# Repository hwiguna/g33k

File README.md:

g33k
====

Personal code, mostly for my blog g33k.blogspot.com

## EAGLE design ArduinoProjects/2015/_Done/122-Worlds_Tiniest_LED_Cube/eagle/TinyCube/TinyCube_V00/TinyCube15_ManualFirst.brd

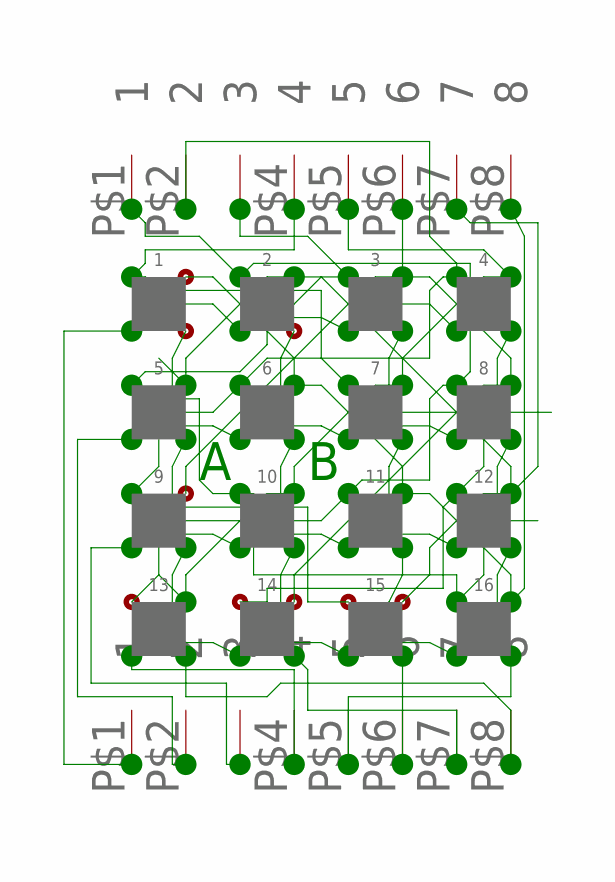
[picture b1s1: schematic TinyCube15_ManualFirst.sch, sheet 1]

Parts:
1, 2, 3, 4, 5, 6, 7, 8, 9, 10, 11, 12, 13, 14, 15, 16: PILLAR; 10MIL
U$51, U$52: TINY_HEADER_DEV; TINY_HEADER_PKG

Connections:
unnamed: 1.R (B), 7.R (B), 12.R (B), 14.R (B), U$52.P$4 (4)
unnamed: 4.B (R), 8.B (R), 12.B (R), 16.B (R), U$51.P$5 (5)
unnamed: 3.B (R), 7.B (R), 11.B (R), 15.B (R), U$51.P$6 (6)
unnamed: 2.B (R), 6.B (R), 10.B (R), 14.B (R), U$51.P$7 (7)
unnamed: 1.+ (G), 6.+ (G), 11.+ (G), 16.+ (G), U$52.P$8 (8)
unnamed: 2.R (B), 8.R (B), 11.R (B), 13.R (B), U$52.P$1 (1)
unnamed: 1.G (A), 2.G (A), 3.G (A), 4.G (A), U$51.P$1 (1)
unnamed: 5.G (A), 6.G (A), 7.G (A), 8.G (A), U$51.P$2 (2)
unnamed: 9.G (A), 10.G (A), 11.G (A), 12.G (A), U$51.P$3 (3)
unnamed: 13.G (A), 14.G (A), 15.G (A), 16.G (A), U$51.P$4 (4)
unnamed: 4.R (B), 6.R (B), 9.R (B), 15.R (B), U$52.P$2 (2)
unnamed: 2.+ (G), 5.+ (G), 12.+ (G), 15.+ (G), U$52.P$7 (7)
unnamed: 3.+ (G), 8.+ (G), 9.+ (G), 14.+ (G), U$52.P$6 (6)
unnamed: 1.B (R), 5.B (R), 9.B (R), 13.B (R), U$51.P$8 (8)
unnamed: 4.+ (G), 7.+ (G), 10.+ (G), 13.+ (G), U$52.P$5 (5)
unnamed: 3.R (B), 5.R (B), 10.R (B), 16.R (B), U$52.P$3 (3)

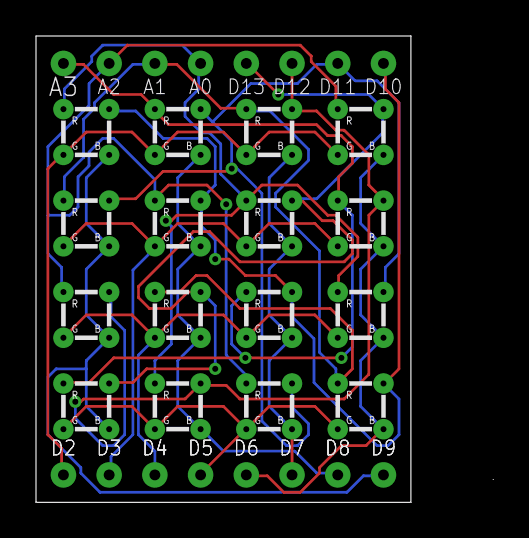
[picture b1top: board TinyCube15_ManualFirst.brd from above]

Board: 2 copper layers, 25.4 x 25.9 mm, 18 parts (0 on the bottom side), 16 nets.

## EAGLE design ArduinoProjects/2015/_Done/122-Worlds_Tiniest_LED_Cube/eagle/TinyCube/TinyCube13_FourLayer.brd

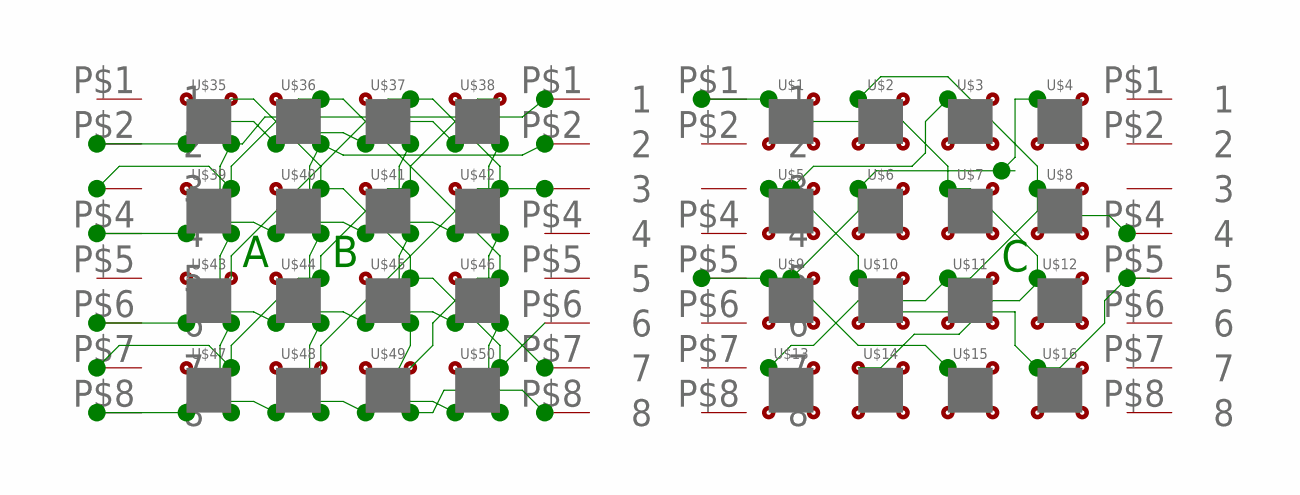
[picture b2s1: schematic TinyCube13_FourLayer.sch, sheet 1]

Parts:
JP1, JP2: TINY_HEADER_DEV; TINY_HEADER_PKG
U$1, U$2, U$3, U$4, U$5, U$6, U$7, U$8, U$9, U$10, U$11, U$12, U$13, U$14, U$15, U$16, U$35, U$36, U$37, U$38, U$39, U$40, U$41, U$42, U$43, U$44, U$45, U$46, U$47, U$48, U$49, U$50: PILLAR; 10MIL
U$51, U$52: TINY_HEADER_DEV; TINY_HEADER_PKG

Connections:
unnamed: JP2.P$4 (4), U$2.R (B), U$8.R (B), U$11.R (B), U$13.R (B)
unnamed: JP1.P$1 (1), U$1.R (B), U$7.R (B), U$12.R (B), U$14.R (B)
unnamed: JP2.P$5 (5), U$3.R (B), U$5.R (B), U$10.R (B), U$16.R (B)
unnamed: JP1.P$5 (5), U$4.R (B), U$6.R (B), U$9.R (B), U$15.R (B)
unnamed: U$35.+ (G), U$40.+ (G), U$45.+ (G), U$50.+ (G), U$52.P$6 (6)
unnamed: U$35.G (A), U$36.G (A), U$37.G (A), U$38.G (A), U$51.P$2 (2)
unnamed: U$39.G (A), U$40.G (A), U$41.G (A), U$42.G (A), U$51.P$4 (4)
unnamed: U$43.G (A), U$44.G (A), U$45.G (A), U$46.G (A), U$51.P$6 (6)
unnamed: U$47.G (A), U$48.G (A), U$49.G (A), U$50.G (A), U$51.P$8 (8)
unnamed: U$35.B (R), U$39.B (R), U$43.B (R), U$47.B (R), U$52.P$1 (1)
unnamed: U$37.B (R), U$41.B (R), U$45.B (R), U$49.B (R), U$52.P$8 (8)
unnamed: U$38.B (R), U$42.B (R), U$46.B (R), U$50.B (R), U$52.P$7 (7)
unnamed: U$36.B (R), U$40.B (R), U$44.B (R), U$48.B (R), U$52.P$2 (2)
unnamed: U$36.+ (G), U$39.+ (G), U$46.+ (G), U$49.+ (G), U$51.P$3 (3)
unnamed: U$37.+ (G), U$42.+ (G), U$43.+ (G), U$48.+ (G), U$52.P$3 (3)
unnamed: U$38.+ (G), U$41.+ (G), U$44.+ (G), U$47.+ (G), U$51.P$7 (7)

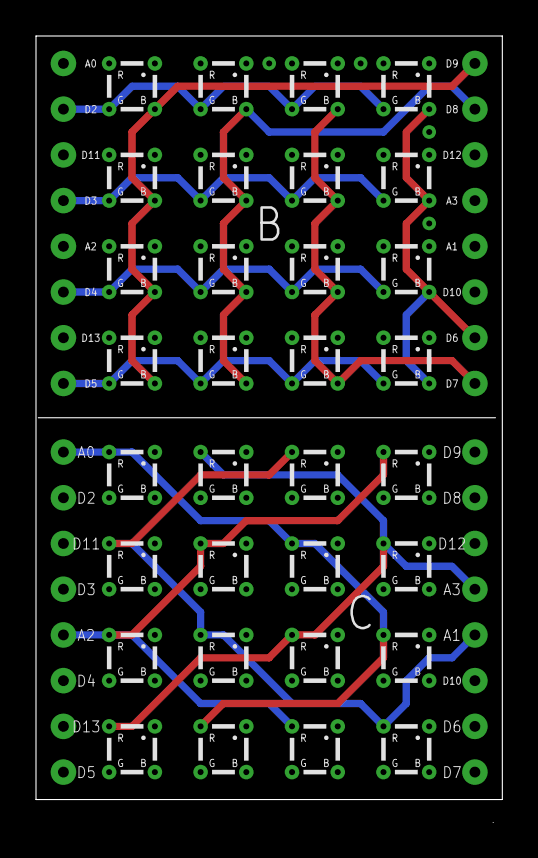
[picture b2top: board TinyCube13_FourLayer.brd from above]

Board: 4 copper layers, 25.9 x 43.7 mm, 36 parts (0 on the bottom side), 16 nets.

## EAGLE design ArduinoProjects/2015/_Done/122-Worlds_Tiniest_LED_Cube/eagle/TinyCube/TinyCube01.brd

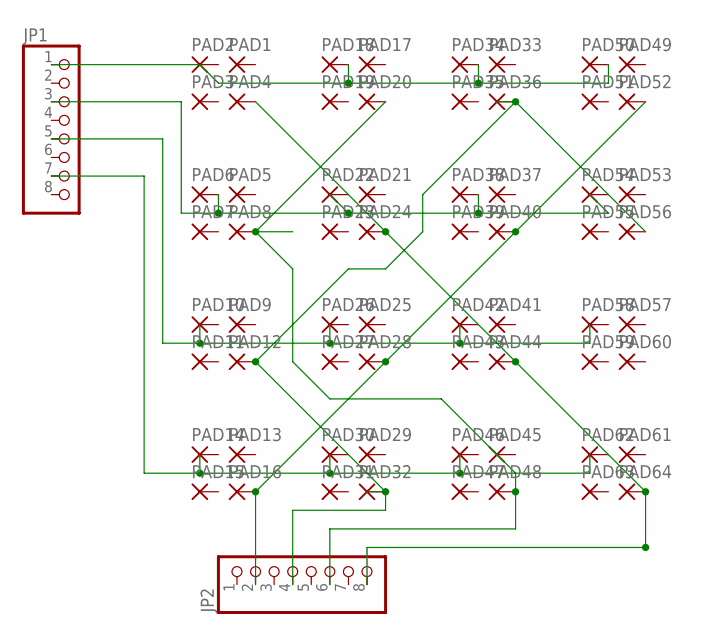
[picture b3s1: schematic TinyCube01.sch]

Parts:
JP1, JP2: PINHD-1X8BIG; 1X08-BIG
PAD1, PAD2, PAD3, PAD4, PAD5, PAD6, PAD7, PAD8, PAD9, PAD10, PAD11, PAD12, PAD13, PAD14, PAD15, PAD16, PAD17, PAD18, PAD19, PAD20, PAD21, PAD22, PAD23, PAD24, PAD25, PAD26, PAD27, PAD28, PAD29, PAD30, PAD31, PAD32, PAD33, PAD34, PAD35, PAD36, PAD37, PAD38, PAD39, PAD40, PAD41, PAD42, PAD43, PAD44, PAD45, PAD46, PAD47, PAD48, PAD49, PAD50, PAD51, PAD52, PAD53, PAD54, PAD55, PAD56, PAD57, PAD58, PAD59, PAD60, PAD61, PAD62, PAD63, PAD64: SMALLPADTHROUGH-HOLE-SMALL; SMALLPAD

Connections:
unnamed: JP2.2, PAD16.1, PAD28.1, PAD40.1, PAD52.1
unnamed: JP2.8, PAD4.1, PAD24.1, PAD44.1, PAD64.1
unnamed: JP2.6, PAD8.1, PAD20.1, PAD48.1
unnamed: JP1.1, PAD18.1, PAD34.1, PAD50.1
unnamed: JP1.3, PAD6.1, PAD38.1
W10: JP2.4, PAD12.1, PAD32.1, PAD36.1, PAD56.1

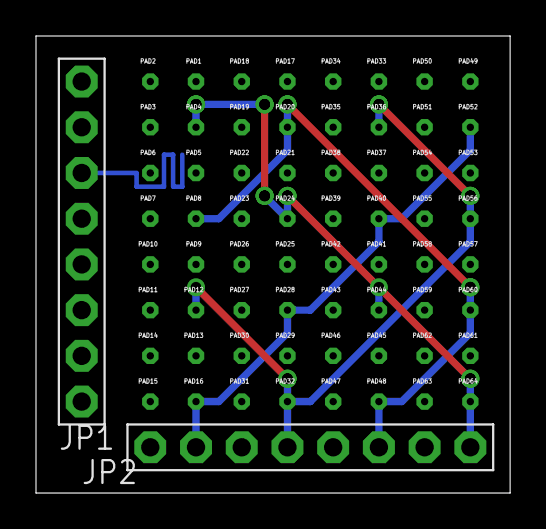
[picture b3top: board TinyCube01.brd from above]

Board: 2 copper layers, 26.3 x 25.4 mm, 66 parts (0 on the bottom side), 6 nets.

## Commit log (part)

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2013-03-22 First version shared on blog
    Uses TIMER, does Fireworks and Bounces.
2013-04-14 First checkin
2014-03-06 Learning how to do interrrupts, figure out the LED matrix pinouts
2014-03-06 Got the shift registers today. Learn how to shift two bytes. Liked MSBFirst shiftOut()
2014-03-07 Move all Tetris related project files into one folder
2014-03-08 Prefix folders with chronological number
2014-03-08 Got interrupt refresh working! Woohoo!
2014-03-08 More comments
2014-03-09 Create and test Tetris shapes
2014-03-10 More analog pins
2014-03-10 Seeing if analogRead works alongside with interrupts
2014-03-10 Let's see if we can control a piece with the accelerometer
2014-03-10 More accelerometer experiments. This one works quite well.
2014-03-10 Figure out when a piece hits something on the bitmap
2014-03-12 Learning how to declare and use class in Arduino
2014-03-14 How to pre-initialize a mumti-dimensional array in a class and return it to main
2014-03-15 This version leaves the pile of shapes that reached bottom
2014-03-15 Rewrote collision checks. Also added check to remove full rows.
2014-03-19 Tweaking the playability
2014-03-23 Playing with keyboard matrix
2014-03-26 Not my code. pushed so i have a backup of my settings
2014-04-14 Sync up HariBot
2014-04-14 Worked on keyboard matrix
2014-04-14 Tweaking Hari's Plotclock
2014-04-26 Goofing around with INPUT_PULLUP
2014-04-27 Beware that this version is for Pololu H-Bridge, different than previous versions!!!
2014-05-10 Syncing mac to github
2014-05-10 Code cleanup
2014-05-12 Playing with Python
2014-05-16 Sync
2014-05-16 Put LED Matrix code on GitHub
2014-06-08 More cube code. Documenting my learning step by step
2014-06-09 Uses TimerOne to refresh cube. Verified some test patterns.
2014-06-30 More cube related revisions
2014-07-03 still playing with interrupts
2014-07-11 Scan one layer for Joseph
2014-07-17 Invert output of shift register because I took transistors off there. More patterns.
2014-07-26 This is what's on completed cube video
2014-07-26 Added three touch sensors and two potentiometers
2014-09-01 Added sine wave animation
2014-09-02 Added transition to sine wave
2014-09-04 Line drawing, Wiper animation.
2014-09-08 Added Bresenham3D line drawing routine
2014-09-08 Experimenting with controlling Arduino from C# via serial
2014-09-08 Corner Bursts Animation
2014-09-10 Split into multiple files. More Animations.
2014-09-15 Flea jump
2014-09-21 Easier to use Flea jump no longer require caller to specify rotation
2014-09-21 We got Rain!
2014-09-23 V15 communication with PC app
2014-09-24 Flea Party !
    Unable to get PC to Arduino serial to work reliably, I worked on
    getting multiple fleas on the cube.
2014-09-29 Preparing for TurbineFlats demo. Added Telekinesis.
2014-10-25 vers 16
2014-10-25 Example
2014-10-25 Trinket version
2014-10-25 Playing with NRF24
2014-10-25 Playing with 4x4 keypad
2014-10-25 Initial push
2014-10-25 crap
2014-10-26 Some missed LED stuff
2014-10-26 Adafruit CC3000 stuff
2014-10-26 missed image
2014-10-26 Auto advance, split source into tabs
2014-10-27 Initial Puzzle
2014-10-27 Learning how to implement classes in Arduino
2014-10-27 AdaFruit Libraries
2014-10-27 Initialize board to a sample puzzle
2014-10-29 Using Candidates and Rejected arrays
2014-10-29 using bits to represent Candidates and Rejected
    because we ran out of RAM when we store those as char arrays
2014-11-01 Implement one CellState instead of separate states for solved and candidates
2014-11-01 Nice class hierarchy: Debug, CellState, Cell, Board, Scaner
2014-11-01 starting to scan
2014-11-01 About to combine Cell and CellState
2014-11-02 OMG it finally worked.
    Stupid mistake making debug take in byte instead of int reported
    erroneous zeroes when passing in int to debug. Also has to pass
    pointers instead of objects so values can be changed.
2014-11-02 Cleanup
2014-11-02 successfully solved a few cells. About to refactor to reuse PruneCells
2014-11-02 refactored so we can use one PruneCells()
2014-11-02 One stinking bit ruined the day. :-(
    Initialization did not initialized enough bits, so 9 was always
    eliminated from the get go.
2014-11-02 Deducing missing one digit working
2014-11-02 Better print2
2014-11-02 ElectSingleCandidates does not work yet, but I want to push this version so I could go back if I need to
2014-11-03 check in so i can work on another machine
2014-11-03 Write an assert function, implemented Election
2014-11-03 Still debugging the Election() routine...
2014-11-03 About to make Asserts optional
2014-11-06 FindClumps partially implemented...
2014-11-06 regular checkin
2014-11-06 Woohoo! It seems to work! More testing needed.
2014-11-07 Refactor Pattern and PatternList. Probably doesn't work yet.
2014-11-07 It works!
2014-11-07 FindInFlocks implemented. Still cannot solve Medium puzzle :-(
2014-11-08 FindUniqueCandidates() finds number that only has one candidate (eventhough candidate cell has other candidates)
2014-11-09 Playing with VisualMicro
2014-11-09 AllCandidatesAreAllInThisFlock
2014-11-09 visual micro
2014-11-09 more debugging work
2014-11-10 checkin
2014-11-10 change puzzle
2014-11-11 Move password to another file
2014-11-12 Build strings and wait for sentinel values
2014-11-16 Checkin before folder cleanup
2014-11-16 b4 folder cleanup
2014-11-16 Move into folder
2014-11-16 Moving into folders
2014-11-16 Fix foldername typo
2014-11-16 More folder reorg
2014-11-26 Learning how to use gitignore
2014-11-26 Various versions of ESDP8266 codes
2014-11-29 LUA Uploader first checkin
2014-11-29 NodeJS and NodeMCU
2014-11-29 Annotated ESP8266 pinouts
2014-11-29 Don't open port at launch, add load from ESP feature
    opening port at launch crashes if the com port is unavailable
2014-11-29 Documentation photos
2014-11-29 updated scripts
2014-11-30 Miscellaneous files
2014-11-30 about to rename the folder itself
2014-11-30 Rename the output to LuaUploader to prevent confusion
2014-11-30 Put in one folder and add compiled and zipped version so people won't have to have VS
2014-12-03 lua scripts
2014-12-03 Learning socket io
2014-12-03 new socket.io supported server
2014-12-05 Circuit diagrams
2014-12-05 Larger image
2014-12-05 Playing with TWO ESPs :-)
2014-12-05 Better startup script from the ESP forum
2014-12-06 New and improved LuaUploader
    Lua source can now be easily Loaded from and Saved to PC
2014-12-06 sync github with my pc
2014-12-06 Lua Uploader 1.0.2
    Port refresh, improved button layout
2014-12-06 forgot the zip version
2014-12-06 Fixed bug where it's no longer restore previously selected port upon relaunch
2014-12-07 More legible font. Commas look like commas instead of periods.
2014-12-08 Start designing the UI for next LUA editor
    Does not work yet
2014-12-09 Fixed bug where I used filename from editor tab in upload tab.
2014-12-13 lua sync
2014-12-13 ESP-03 driving a 7-segment display via a Shift Register
    Shared on YouTube.
2014-12-14 LED resistors should be 220ohms. Clarify how to wire subsequent shift registers.
2014-12-14 Label more parts and pins to clarify
2014-12-15 $3 Wifi module part 9: X-10 Hacking
2014-12-18 Cool trick
2014-12-19 Rube goldberg is working!
2014-12-19 more lua
2014-12-19 shortcuts
2014-12-22 Still trying to figure out why power drops when more than one ESP is in same circuit.
2014-12-22 Misc sync
2015-01-03 Diagram
2015-01-03 Move Shift Register code to its own folder
2015-01-03 Initial checkin of WorldWideESP. Basic TX-RX
2015-01-19 Learning Kicad
2015-01-19 Implemented load from ESP
    Thanks to Eskici for the code to extract the lua code sent back by the
    ESP!
2015-01-27 No need to put AdaFruit's libraries my folder.
2015-01-27 Playing with $4 Arduino OLED Display
2015-01-27 Code for $4 Arduino OLED Display video on Youtube
    https://www.youtube.com/watch?v=_t_lfcGV_YM
2015-02-04 HariFun #101 - Scope Club 1 - Drawing graphics on an Oscilloscope using an Arduino Nano
2015-02-05 Playing with MOSFET
2015-02-05 Direct port manipulation
2015-02-08 ScopeClub Episode 2 files
2015-02-09 Fixed bug where writing to file doesn't work when lua source ends in square bracket
2015-02-09 Include ready-to-run version with the bugfix
2015-02-13 checkin in file to work downstairs
2015-03-05 Adjust UI element anchors so it would fit on a 1024 pixel wide screens
2015-03-07 Trying to get reliably request from ESP to NodejS on PI
2015-03-09 Fix laptop size, make panes resizable
2015-03-15 Working on Zero to IoT video
2015-03-21 Sync ESP8266 stuff
2015-03-21 Seven Segment Clock for Jay
2015-03-23 sync
    End to end works, but still buggy
2015-03-23 Use DS3231 library
2015-03-25 Yes another DS3231 library. IMPORTANT: Make sure you only have ONE DS3231 library. This has the same name as another DS3231.
2015-03-28 Use TimerOne interrupt library instead of loop()
2015-03-30 Added 12hour mode, blinking colon, PM indicator.
2015-03-30 Update latest TimerOne version to use AdaFruit RTC library because the Jarzebski library always sets time to compile time upon reset!
2015-04-03 Fixed wiring error. Thanks to Ian Brown for catching my mistake!
2015-04-03 Comment out prints because they seem to slow down the response time.
2015-04-15 Folder cleanup
2015-04-28 attempt
2015-04-28 Helping Jay
2015-04-28 Playing with ESP-12
2015-04-28 Playing with compass module
2015-05-01 AbsoluteIMU
2015-05-07 sync mac
2015-05-10 Shared with youtubers
2015-05-25 HariFun #109 One Way Chat
2015-05-25 rename folder
2015-06-15 Welcome to MakeShift Lincoln
2015-07-11 HariFun #114 - Made in USA
2015-07-12 init
2015-07-12 moving stuff around
2015-07-12 icon
2015-07-12 sync 109
2015-07-12 sync 110
2015-07-12 sync learning
2015-07-12 sync misc
2015-07-12 folder
2015-07-13 Learning SPI on Arduino and ATTiny
2015-07-17 still working in this
2015-07-20 Remove custom demo chars, implement PrintAt()
2015-08-02 Chords on ESP!
2015-08-05 Move to _Done
2015-08-10 startup issue
2015-08-15 10 buttons read via pin change interrupt, now working on Sleep()
2015-08-18 unsigned char for the fake PORTD command and keep CS_PIN low at all times
2015-08-21 remap so we don't have to change IRlib pins
2015-08-24 Start using IRLib
2015-08-24 Can decode IR, save to EEPROM, recall and send IR upon button. Still lots of bugs.
2015-08-24 More helpful startup message
2015-08-24 The PC and Arduino pair now works. Still need tons of error handling.
2015-08-24 Added zipped compiled app so you don't need Visual Studio to play with this
2015-09-01 Learning how to draw
2015-09-02 We can now display date and time on the OLED!
2015-09-02 Month and Date was swapped. Oops...
2015-09-02 Even larger fonts
2015-09-02 bettter url
2015-09-07 eagle
2015-09-07 nano+ rtc
2015-09-07 Fix year
2015-09-13 lost and found old projects
2015-09-17 lasercut plans
2015-09-20 Beep is on D13, same as LED
2015-09-20 This 08b is the one sent to Papi
2015-09-20 Shown at MakeLincoln 2015
2015-09-20 Playing with eagleCAD
2015-09-22 Final lasercut case
2015-09-26 First stab
2015-10-05 Checkin for youtube
    Still lots to do.
2015-10-05 Be consistent with YouTube
2015-10-11 ESP Matrix
2015-10-13 From blink to pong!
2015-10-17 Final
2015-10-25 bugfix
2015-10-25 J increased delay
2015-11-16 Cleanup folder
2015-11-20 for j
2015-11-20 Arduino 101
2015-11-20 better label
2015-12-11 Common Anode Charliecube!
2015-12-13 Links to download device drivers
2015-12-13 rename to reorder folders
2015-12-25 cube backup
2015-12-28 Shared version
2016-01-09 vers13 (four layers!)
2016-01-15 cube sync
2016-01-20 sync for J
2016-02-04 Version 0
2016-02-04 What's shown in video
2016-02-11 Thanks
2016-02-20 First version
2016-02-22 sync jig files
2016-03-07 learning about SPIFFS
2016-03-13 first
2016-03-28 Playing with PCF8574
2016-04-06 works
2016-06-01 make it shorter
2016-06-01 even shorter
2016-06-03 speed up and scoring
2016-06-13 backup to cloud
2016-06-16 pong5
2016-06-25 it's working!
2016-07-28 Don't enable interrupt until current IR is done
2017-09-22 Added Zip of version 16 for easy downloading
2018-12-27 Fixed bug caused by hour 2x is drawn outside screen
    Do not shift one to left when showing hour 2x:xx. 2 will run into the
    next hour digit, but probably would look ok. Thanks to Dorin Nicoara for
    finding and explaining the cause of this bug
